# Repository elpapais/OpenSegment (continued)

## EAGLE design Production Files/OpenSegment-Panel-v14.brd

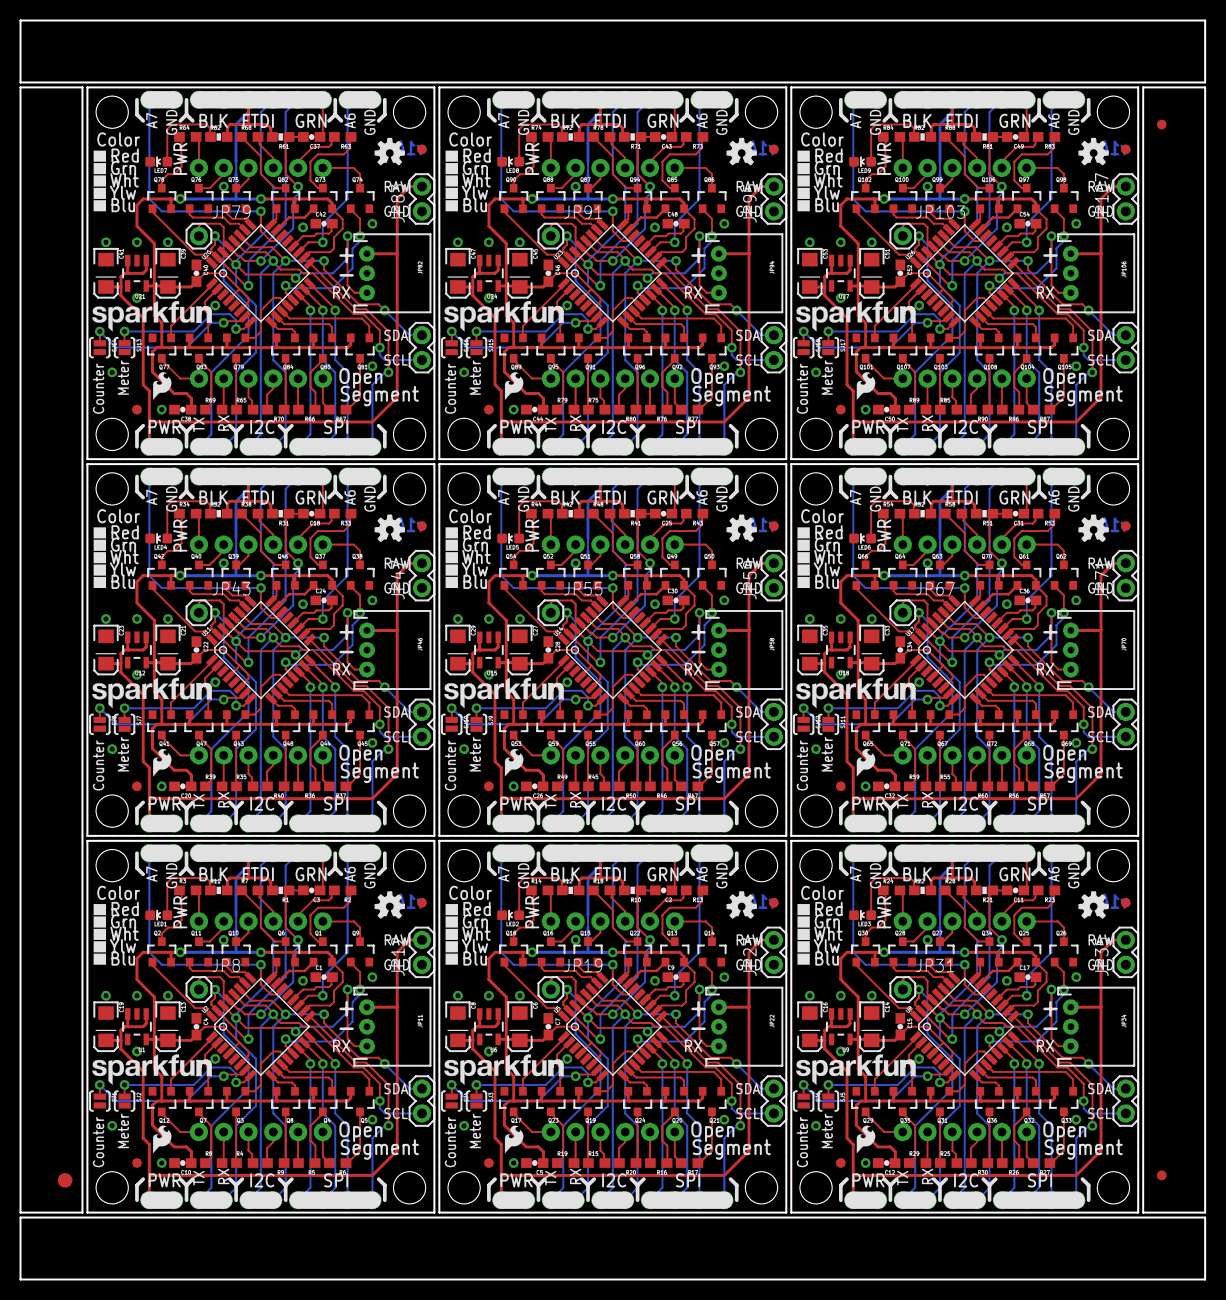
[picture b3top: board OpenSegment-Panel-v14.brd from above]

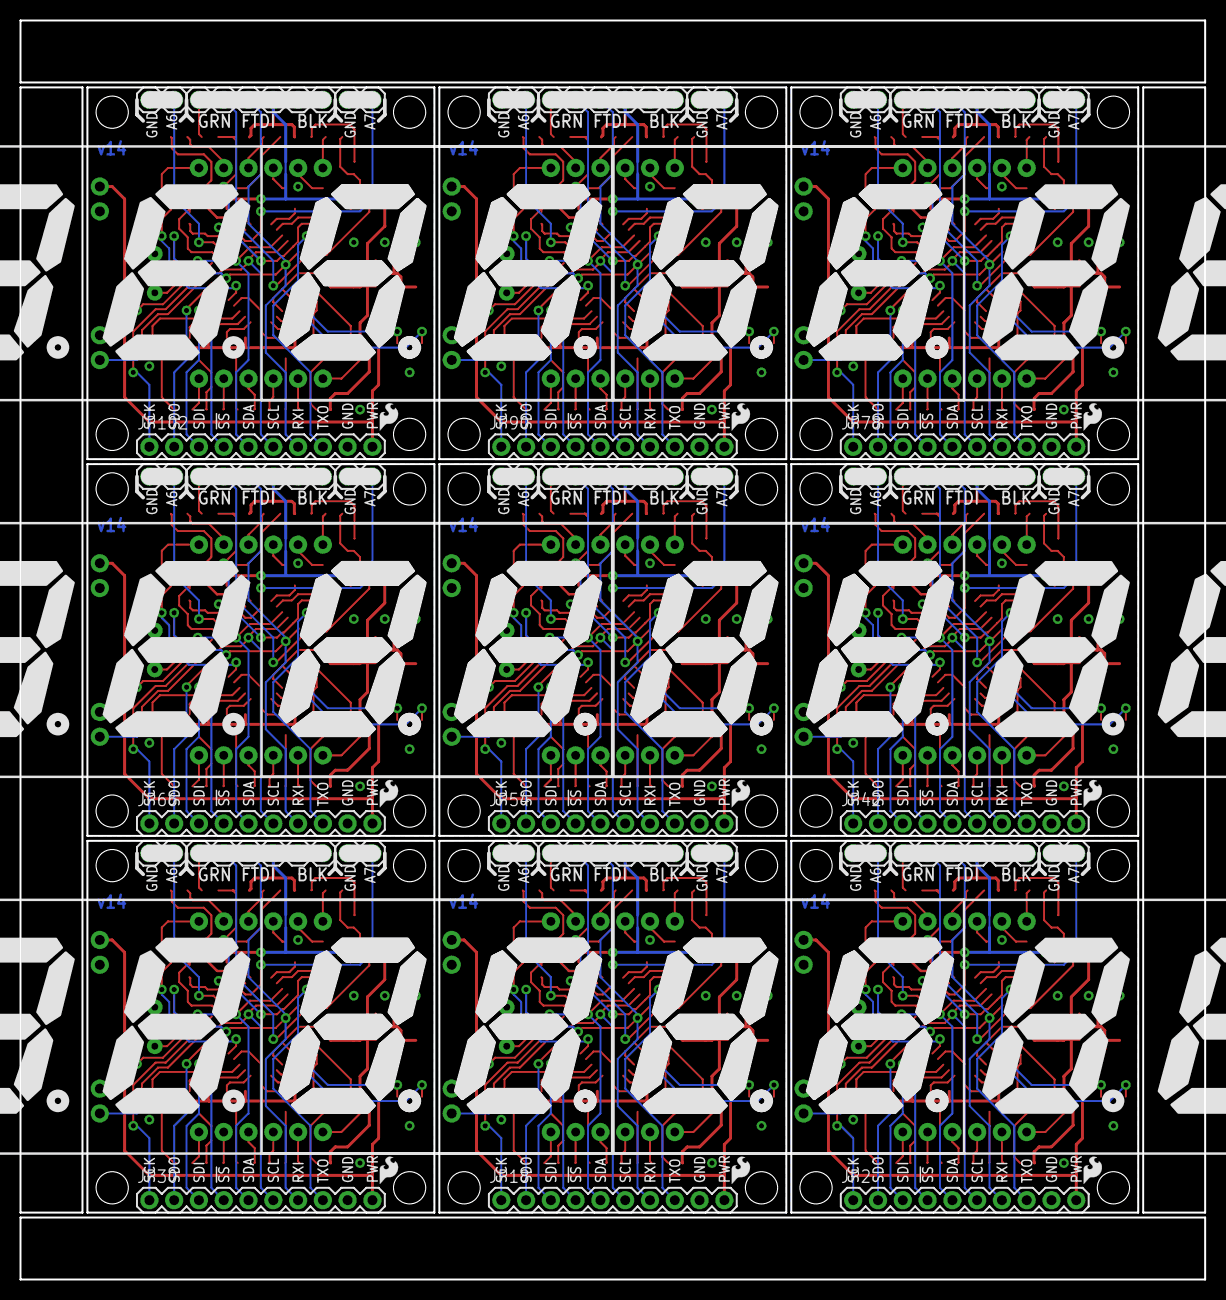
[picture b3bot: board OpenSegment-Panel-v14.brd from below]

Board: 2 copper layers, 121.4 x 129.0 mm, 471 parts (54 on the bottom side), 459 nets.

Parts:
C1, C2, C3, C4, C7, C9, C11, C15, C17, C18, C22, C24, C25, C28, C30, C31, C34, C36, C37, C40, C42, C43, C46, C48, C49, C52, C54: 0.1uF; 0603-CAP
C5, C10, C12, C20, C26, C32, C38, C44, C50: 1uF; 0603-CAP
C6, C8, C13, C14, C16, C19, C21, C23, C27, C29, C33, C35, C39, C41, C45, C47, C51, C53: 10uF; EIA3216
E$1: FIDUCIAL-1.5X3
E$4, E$5: FIDUCIAL-1X2
FID1, FID2, FID3, FID4, FID5, FID6, FID7, FID8, FID9, FID10, FID11, FID12, FID13, FID14, FID15, FID16, FID17, FID18: FIDUCIAL1X2; FIDUCIAL-1X2
JP1, JP7, JP25, JP37, JP49, JP61, JP73, JP85, JP97: FTDI_BASIC
JP2, JP18, JP30, JP42, JP54, JP66, JP78, JP90, JP102: Connections; 1X10
JP3, JP4, JP5, JP6, JP14, JP15, JP16, JP17, JP26, JP27, JP28, JP29, JP38, JP39, JP40, JP41, JP50, JP51, JP52, JP53, JP62, JP63, JP64, JP65, JP74, JP75, JP76, JP77, JP86, JP87, JP88, JP89, JP98, JP99, JP100, JP101: STAND-OFF
JP8, JP19, JP31, JP43, JP55, JP67, JP79, JP91, JP103: RESET; 1X01
JP9, JP10, JP12, JP13, JP20, JP21, JP23, JP24, JP32, JP33, JP35, JP36, JP44, JP45, JP47, JP48, JP56, JP57, JP59, JP60, JP68, JP69, JP71, JP72, JP80, JP81, JP83, JP84, JP92, JP93, JP95, JP96, JP104, JP105, JP107, JP108: 1X02
JP11, JP22, JP34, JP46, JP58, JP70, JP82, JP94, JP106: Serial; JST-3-PTH
LED1, LED2, LED3, LED4, LED5, LED6, LED7, LED8, LED9: Red; LED-0603
Q1, Q2, Q3, Q4, Q5, Q6, Q7, Q8, Q13, Q18, Q19, Q20, Q21, Q22, Q23, Q24, Q25, Q30, Q31, Q32, Q33, Q34, Q35, Q36, Q37, Q42, Q43, Q44, Q45, Q46, Q47, Q48, Q49, Q54, Q55, Q56, Q57, Q58, Q59, Q60, Q61, Q66, Q67, Q68, Q69, Q70, Q71, Q72, Q73, Q78, Q79, Q80, Q81, Q82, Q83, Q84, Q85, Q90, Q91, Q92, Q93, Q94, Q95, Q96, Q97, Q102, Q103, Q104, Q105, Q106, Q107, Q108: PNP; SOT23-3
Q9, Q10, Q11, Q12, Q14, Q15, Q16, Q17, Q26, Q27, Q28, Q29, Q38, Q39, Q40, Q41, Q50, Q51, Q52, Q53, Q62, Q63, Q64, Q65, Q74, Q75, Q76, Q77, Q86, Q87, Q88, Q89, Q98, Q99, Q100, Q101: MMBT2222; SOT23-3
R1, R10, R21, R31, R41, R51, R61, R71, R81: 10k; 0603-RES
R2, R3, R4, R5, R6, R7, R8, R9, R13, R14, R15, R16, R17, R18, R19, R20, R23, R24, R25, R26, R27, R28, R29, R30, R33, R34, R35, R36, R37, R38, R39, R40, R43, R44, R45, R46, R47, R48, R49, R50, R53, R54, R55, R56, R57, R58, R59, R60, R63, R64, R65, R66, R67, R68, R69, R70, R73, R74, R75, R76, R77, R78, R79, R80, R83, R84, R85, R86, R87, R88, R89, R90: 33/68; 0603
R11, R12, R22, R32, R42, R52, R62, R72, R82: 330; 0603-RES
SJ1, SJ2, SJ3, SJ4, SJ5, SJ6, SJ7, SJ8, SJ9, SJ10, SJ11, SJ12, SJ13, SJ14, SJ15, SJ16, SJ17, SJ18: Counter Ctl; SJ_2S-NO
U1, U6, U9, U12, U15, U18, U21, U24, U27: MIC5219; SOT23-5
U2, U5, U8, U11, U14, U17, U20, U23, U26: ATMEGA328; TQFP32-08
U3, U4, U7, U10, U13, U16, U19, U22, U25: 7-SEGMENT-4DIGIT-COUNTERPTH; 7-SEGMENT-4DIGIT-COUNTER
U$1, U$2, U$5, U$6, U$10, U$11, U$14, U$15, U$18, U$19, U$22, U$23, U$26, U$27, U$30, U$31, U$34, U$35: LOGO-SFESK; SFE-LOGO-FLAME
U$3, U$7, U$9, U$13, U$17, U$21, U$25, U$29, U$33: LOGO-SFENW2; SFE-NEW-WEB
U$4, U$8, U$12, U$16, U$20, U$24, U$28, U$32, U$36: OSHW-LOGOS; OSHW-LOGO-S

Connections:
!SS: JP2.4, U2.14
!SS1: JP18.4, U5.14
!SS2: JP30.4, U8.14
!SS3: JP42.4, U11.14
!SS4: JP54.4, U14.14
!SS5: JP66.4, U17.14
!SS6: JP78.4, U20.14
!SS7: JP90.4, U23.14
!SS8: JP102.4, U26.14
A1: JP20.2, U5.19
A2: JP21.2, U5.22
A3: JP32.2, U8.19
A4: JP33.2, U8.22
A5: JP44.2, U11.19
A6: JP9.2, U2.19
A7: JP10.2, U2.22
A8: JP45.2, U11.22
A9: JP56.2, U14.19
A10: JP57.2, U14.22
A11: JP68.2, U17.19
A12: JP69.2, U17.22
A13: JP80.2, U20.19
A14: JP81.2, U20.22
A15: JP92.2, U23.19
A16: JP93.2, U23.22
A17: JP104.2, U26.19
A18: JP105.2, U26.22
ANALOG: SJ2.1, U2.8
ANALOG1: SJ3.1, U5.8
ANALOG2: SJ5.1, U8.8
ANALOG3: SJ7.1, U11.8
ANALOG4: SJ9.1, U14.8
ANALOG5: SJ11.1, U17.8
ANALOG6: SJ13.1, U20.8
ANALOG7: SJ15.1, U23.8
ANALOG8: SJ17.1, U26.8
C-DIG1: Q9.1, U2.13
C-DIG2: Q10.1, U2.25
C-DIG3: Q11.1, U2.26
C-DIG4: Q12.1, U2.1
C-DIG5: Q14.1, U5.13
C-DIG6: Q15.1, U5.25
C-DIG7: Q16.1, U5.26
C-DIG8: Q17.1, U5.1
C-DIG9: Q26.1, U8.13
C-DIG10: Q27.1, U8.25
C-DIG11: Q28.1, U8.26
C-DIG12: Q29.1, U8.1
C-DIG13: Q38.1, U11.13
C-DIG14: Q39.1, U11.25
C-DIG15: Q40.1, U11.26
C-DIG16: Q41.1, U11.1
C-DIG17: Q50.1, U14.13
C-DIG18: Q51.1, U14.25
C-DIG19: Q52.1, U14.26
C-DIG20: Q53.1, U14.1
C-DIG21: Q62.1, U17.13
C-DIG22: Q63.1, U17.25
C-DIG23: Q64.1, U17.26
C-DIG24: Q65.1, U17.1
C-DIG25: Q74.1, U20.13
C-DIG26: Q75.1, U20.25
C-DIG27: Q76.1, U20.26
C-DIG28: Q77.1, U20.1
C-DIG29: Q86.1, U23.13
C-DIG30: Q87.1, U23.25
C-DIG31: Q88.1, U23.26
C-DIG32: Q89.1, U23.1
C-DIG33: Q98.1, U26.13
C-DIG34: Q99.1, U26.25
C-DIG35: Q100.1, U26.26
C-DIG36: Q101.1, U26.1
C-SEGA: Q1.1, U2.23
C-SEGA1: Q13.1, U5.23
C-SEGA2: Q25.1, U8.23
C-SEGA3: Q37.1, U11.23
C-SEGA4: Q49.1, U14.23
C-SEGA5: Q61.1, U17.23
C-SEGA6: Q73.1, U20.23
C-SEGA7: Q85.1, U23.23
C-SEGA8: Q97.1, U26.23
C-SEGB: Q2.1, U2.32
C-SEGB1: Q18.1, U5.32
C-SEGB2: Q30.1, U8.32
C-SEGB3: Q42.1, U11.32
C-SEGB4: Q54.1, U14.32
C-SEGB5: Q66.1, U17.32
C-SEGB6: Q78.1, U20.32
C-SEGB7: Q90.1, U23.32
C-SEGB8: Q102.1, U26.32
C-SEGC: Q3.1, U2.12
C-SEGC1: Q19.1, U5.12
C-SEGC2: Q31.1, U8.12
C-SEGC3: Q43.1, U11.12
C-SEGC4: Q55.1, U14.12
C-SEGC5: Q67.1, U17.12
C-SEGC6: Q79.1, U20.12
C-SEGC7: Q91.1, U23.12
C-SEGC8: Q103.1, U26.12
C-SEGD: Q4.1, U2.10
C-SEGD1: Q20.1, U5.10
C-SEGD2: Q32.1, U8.10
C-SEGD3: Q44.1, U11.10
C-SEGD4: Q56.1, U14.10
C-SEGD5: Q68.1, U17.10
C-SEGD6: Q80.1, U20.10
C-SEGD7: Q92.1, U23.10
C-SEGD8: Q104.1, U26.10
C-SEGDP: Q8.1, U2.9
C-SEGDP1: Q24.1, U5.9
C-SEGDP2: Q36.1, U8.9
C-SEGDP3: Q48.1, U11.9
C-SEGDP4: Q60.1, U14.9
C-SEGDP5: Q72.1, U17.9
C-SEGDP6: Q84.1, U20.9
C-SEGDP7: Q96.1, U23.9
C-SEGDP8: Q108.1, U26.9
C-SEGE: Q5.1, U2.11
C-SEGE1: Q21.1, U5.11
C-SEGE2: Q33.1, U8.11
C-SEGE3: Q45.1, U11.11
C-SEGE4: Q57.1, U14.11
C-SEGE5: Q69.1, U17.11
C-SEGE6: Q81.1, U20.11
C-SEGE7: Q93.1, U23.11
C-SEGE8: Q105.1, U26.11
C-SEGF: Q6.1, U2.24
C-SEGF1: Q22.1, U5.24
C-SEGF2: Q34.1, U8.24
C-SEGF3: Q46.1, U11.24
C-SEGF4: Q58.1, U14.24
C-SEGF5: Q70.1, U17.24
C-SEGF6: Q82.1, U20.24
C-SEGF7: Q94.1, U23.24
C-SEGF8: Q106.1, U26.24
C-SEGG: Q7.1, U2.2
C-SEGG1: Q23.1, U5.2
C-SEGG2: Q35.1, U8.2
C-SEGG3: Q47.1, U11.2
C-SEGG4: Q59.1, U14.2
C-SEGG5: Q71.1, U17.2
C-SEGG6: Q83.1, U20.2
C-SEGG7: Q95.1, U23.2
C-SEGG8: Q107.1, U26.2
COUNTER: SJ1.1, U2.7
COUNTER1: SJ4.1, U5.7
COUNTER2: SJ6.1, U8.7
COUNTER3: SJ8.1, U11.7
COUNTER4: SJ10.1, U14.7
COUNTER5: SJ12.1, U17.7
COUNTER6: SJ14.1, U20.7
COUNTER7: SJ16.1, U23.7
COUNTER8: SJ18.1, U26.7
DIG1: Q9.3, U3.12
DIG2: Q10.3, U3.9
DIG3: Q11.3, U3.8
DIG4: Q12.3, U3.6
DIG5: Q14.3, U4.12
DIG6: Q15.3, U4.9
DIG7: Q16.3, U4.8
DIG8: Q17.3, U4.6
DIG9: Q26.3, U7.12
DIG10: Q27.3, U7.9
DIG11: Q28.3, U7.8
DIG12: Q29.3, U7.6
DIG13: Q38.3, U10.12
DIG14: Q39.3, U10.9
DIG15: Q40.3, U10.8
DIG16: Q41.3, U10.6
DIG17: Q50.3, U13.12
DIG18: Q51.3, U13.9
DIG19: Q52.3, U13.8
DIG20: Q53.3, U13.6
DIG21: Q62.3, U16.12
DIG22: Q63.3, U16.9
DIG23: Q64.3, U16.8
DIG24: Q65.3, U16.6
DIG25: Q74.3, U19.12
DIG26: Q75.3, U19.9
DIG27: Q76.3, U19.8
DIG28: Q77.3, U19.6
DIG29: Q86.3, U22.12
DIG30: Q87.3, U22.9
DIG31: Q88.3, U22.8
DIG32: Q89.3, U22.6
DIG33: Q98.3, U25.12
DIG34: Q99.3, U25.9
DIG35: Q100.3, U25.8
DIG36: Q101.3, U25.6
GND: C1.1, C4.1, C10.2, C13.C, C19.C, JP1.GND, JP2.9, JP9.1, JP10.1, JP11.2, JP12.1, LED1.C, Q9.2, Q10.2, Q11.2, Q12.2, SJ1.2, SJ2.2, U1.2, U2.3, U2.5, U2.21
GND1: C5.2, C6.C, C7.1, C8.C, C9.1, JP7.GND, JP18.9, JP20.1, JP21.1, JP22.2, JP23.1, LED2.C, Q14.2, Q15.2, Q16.2, Q17.2, SJ3.2, SJ4.2, U5.3, U5.5, U5.21, U6.2
GND2: C12.2, C14.C, C15.1, C16.C, C17.1, JP25.GND, JP30.9, JP32.1, JP33.1, JP34.2, JP35.1, LED3.C, Q26.2, Q27.2, Q28.2, Q29.2, SJ5.2, SJ6.2, U8.3, U8.5, U8.21, U9.2
GND3: C20.2, C21.C, C22.1, C23.C, C24.1, JP37.GND, JP42.9, JP44.1, JP45.1, JP46.2, JP47.1, LED4.C, Q38.2, Q39.2, Q40.2, Q41.2, SJ7.2, SJ8.2, U11.3, U11.5, U11.21, U12.2
GND4: C26.2, C27.C, C28.1, C29.C, C30.1, JP49.GND, JP54.9, JP56.1, JP57.1, JP58.2, JP59.1, LED5.C, Q50.2, Q51.2, Q52.2, Q53.2, SJ9.2, SJ10.2, U14.3, U14.5, U14.21, U15.2
GND5: C32.2, C33.C, C34.1, C35.C, C36.1, JP61.GND, JP66.9, JP68.1, JP69.1, JP70.2, JP71.1, LED6.C, Q62.2, Q63.2, Q64.2, Q65.2, SJ11.2, SJ12.2, U17.3, U17.5, U17.21, U18.2
GND6: C38.2, C39.C, C40.1, C41.C, C42.1, JP73.GND, JP78.9, JP80.1, JP81.1, JP82.2, JP83.1, LED7.C, Q74.2, Q75.2, Q76.2, Q77.2, SJ13.2, SJ14.2, U20.3, U20.5, U20.21, U21.2
GND7: C44.2, C45.C, C46.1, C47.C, C48.1, JP85.GND, JP90.9, JP92.1, JP93.1, JP94.2, JP95.1, LED8.C, Q86.2, Q87.2, Q88.2, Q89.2, SJ15.2, SJ16.2, U23.3, U23.5, U23.21, U24.2
GND8: C50.2, C51.C, C52.1, C53.C, C54.1, JP97.GND, JP102.9, JP104.1, JP105.1, JP106.2, JP107.1, LED9.C, Q98.2, Q99.2, Q100.2, Q101.2, SJ17.2, SJ18.2, U26.3, U26.5, U26.21, U27.2
unnamed: Q1.3, R2.1
unnamed: C2.1, JP7.DTR
unnamed: C3.1, JP1.DTR
unnamed: Q2.3, R3.1
unnamed: Q3.3, R4.1
unnamed: Q4.3, R5.1
unnamed: Q5.3, R6.1
unnamed: Q6.3, R7.1
unnamed: Q7.3, R8.1
unnamed: Q8.3, R9.1
unnamed: C1.2, U2.20
unnamed: LED2.A, R12.1
unnamed: Q13.3, R13.1
unnamed: Q18.3, R14.1
unnamed: Q19.3, R15.1
unnamed: Q20.3, R16.1
unnamed: Q21.3, R17.1
unnamed: Q22.3, R18.1
unnamed: Q23.3, R19.1
unnamed: Q24.3, R20.1
unnamed: C9.2, U5.20
unnamed: C11.1, JP25.DTR
unnamed: LED3.A, R22.1
unnamed: Q25.3, R23.1
unnamed: Q30.3, R24.1
unnamed: Q31.3, R25.1
unnamed: Q32.3, R26.1
unnamed: Q33.3, R27.1
unnamed: Q34.3, R28.1
unnamed: Q35.3, R29.1
unnamed: Q36.3, R30.1
unnamed: C17.2, U8.20
unnamed: C18.1, JP37.DTR
unnamed: LED4.A, R32.1
unnamed: Q37.3, R33.1
unnamed: Q42.3, R34.1
unnamed: Q43.3, R35.1
unnamed: LED1.A, R11.1
unnamed: Q44.3, R36.1
unnamed: Q45.3, R37.1
unnamed: Q46.3, R38.1
unnamed: Q47.3, R39.1
unnamed: Q48.3, R40.1
unnamed: C24.2, U11.20
unnamed: C25.1, JP49.DTR
unnamed: LED5.A, R42.1
unnamed: Q49.3, R43.1
unnamed: Q54.3, R44.1
unnamed: Q55.3, R45.1
unnamed: Q56.3, R46.1
unnamed: Q57.3, R47.1
unnamed: Q58.3, R48.1
unnamed: Q59.3, R49.1
unnamed: Q60.3, R50.1
unnamed: C30.2, U14.20
unnamed: C31.1, JP61.DTR
unnamed: LED6.A, R52.1
unnamed: Q61.3, R53.1
unnamed: Q66.3, R54.1
unnamed: Q67.3, R55.1
unnamed: Q68.3, R56.1
unnamed: Q69.3, R57.1
unnamed: Q70.3, R58.1
unnamed: Q71.3, R59.1
unnamed: Q72.3, R60.1
unnamed: C36.2, U17.20
unnamed: C37.1, JP73.DTR
unnamed: LED7.A, R62.1
unnamed: Q73.3, R63.1
unnamed: Q78.3, R64.1
unnamed: Q79.3, R65.1
unnamed: Q80.3, R66.1
unnamed: Q81.3, R67.1
unnamed: Q82.3, R68.1
unnamed: Q83.3, R69.1
unnamed: Q84.3, R70.1
unnamed: C42.2, U20.20
unnamed: C43.1, JP85.DTR
unnamed: LED8.A, R72.1
unnamed: Q85.3, R73.1
unnamed: Q90.3, R74.1
unnamed: Q91.3, R75.1
unnamed: Q92.3, R76.1
unnamed: Q93.3, R77.1
unnamed: Q94.3, R78.1
unnamed: Q95.3, R79.1
unnamed: Q96.3, R80.1
unnamed: C48.2, U23.20
unnamed: C49.1, JP97.DTR
unnamed: LED9.A, R82.1
unnamed: Q97.3, R83.1
unnamed: Q102.3, R84.1
unnamed: Q103.3, R85.1
unnamed: Q104.3, R86.1
unnamed: Q105.3, R87.1
unnamed: Q106.3, R88.1
unnamed: Q107.3, R89.1
unnamed: Q108.3, R90.1
unnamed: C54.2, U26.20
RAW: C19.A, JP2.10, JP11.1, JP12.2, U1.1, U1.3
RAW1: C8.A, JP18.10, JP22.1, JP23.2, U6.1, U6.3
RAW2: C16.A, JP30.10, JP34.1, JP35.2, U9.1, U9.3
RAW3: C23.A, JP42.10, JP46.1, JP47.2, U12.1, U12.3
RAW4: C29.A, JP54.10, JP58.1, JP59.2, U15.1, U15.3
RAW5: C35.A, JP66.10, JP70.1, JP71.2, U18.1, U18.3
RAW6: C41.A, JP78.10, JP82.1, JP83.2, U21.1, U21.3
RAW7: C47.A, JP90.10, JP94.1, JP95.2, U24.1, U24.3
RAW8: C53.A, JP102.10, JP106.1, JP107.2, U27.1, U27.3
RST: C3.2, JP8.1, R1.1, U2.29
RST1: C2.2, JP19.1, R10.1, U5.29
RST2: C11.2, JP31.1, R21.1, U8.29
RST3: C18.2, JP43.1, R31.1, U11.29
RST4: C25.2, JP55.1, R41.1, U14.29
RST5: C31.2, JP67.1, R51.1, U17.29
RST6: C37.2, JP79.1, R61.1, U20.29
RST7: C43.2, JP91.1, R71.1, U23.29
RST8: C49.2, JP103.1, R81.1, U26.29
RXI: JP1.TXO, JP2.7, JP11.3, U2.30
RXI1: JP7.TXO, JP18.7, JP22.3, U5.30
RXI2: JP25.TXO, JP30.7, JP34.3, U8.30
RXI3: JP37.TXO, JP42.7, JP46.3, U11.30
RXI4: JP49.TXO, JP54.7, JP58.3, U14.30
RXI5: JP61.TXO, JP66.7, JP70.3, U17.30
RXI6: JP73.TXO, JP78.7, JP82.3, U20.30
RXI7: JP85.TXO, JP90.7, JP94.3, U23.30
RXI8: JP97.TXO, JP102.7, JP106.3, U26.30
SCK: JP2.1, U2.17
SCK1: JP18.1, U5.17
SCK2: JP30.1, U8.17
SCK3: JP42.1, U11.17
SCK4: JP54.1, U14.17
SCK5: JP66.1, U17.17
SCK6: JP78.1, U20.17
SCK7: JP90.1, U23.17
SCK8: JP102.1, U26.17
SCL: JP2.6, JP13.2, U2.28
SCL1: JP18.6, JP24.2, U5.28
SCL2: JP30.6, JP36.2, U8.28
SCL3: JP42.6, JP48.2, U11.28
SCL4: JP54.6, JP60.2, U14.28
SCL5: JP66.6, JP72.2, U17.28
SCL6: JP78.6, JP84.2, U20.28
SCL7: JP90.6, JP96.2, U23.28
SCL8: JP102.6, JP108.2, U26.28
SDA: JP2.5, JP13.1, U2.27
SDA1: JP18.5, JP24.1, U5.27
SDA2: JP30.5, JP36.1, U8.27
SDA3: JP42.5, JP48.1, U11.27
SDA4: JP54.5, JP60.1, U14.27
SDA5: JP66.5, JP72.1, U17.27
SDA6: JP78.5, JP84.1, U20.27
SDA7: JP90.5, JP96.1, U23.27
SDA8: JP102.5, JP108.1, U26.27
SDI: JP2.3, U2.15
SDI1: JP18.3, U5.15
SDI2: JP30.3, U8.15
SDI3: JP42.3, U11.15
SDI4: JP54.3, U14.15
SDI5: JP66.3, U17.15
SDI6: JP78.3, U20.15
SDI7: JP90.3, U23.15
SDI8: JP102.3, U26.15
SDO: JP2.2, U2.16
SDO1: JP18.2, U5.16
SDO2: JP30.2, U8.16
SDO3: JP42.2, U11.16
SDO4: JP54.2, U14.16
SDO5: JP66.2, U17.16
SDO6: JP78.2, U20.16
SDO7: JP90.2, U23.16
SDO8: JP102.2, U26.16
SEGA: R2.2, U3.11
SEGA1: R13.2, U4.11
SEGA2: R23.2, U7.11
SEGA3: R33.2, U10.11
SEGA4: R43.2, U13.11
SEGA5: R53.2, U16.11
SEGA6: R63.2, U19.11
SEGA7: R73.2, U22.11
SEGA8: R83.2, U25.11
SEGB: R3.2, U3.7
SEGB1: R14.2, U4.7
SEGB2: R24.2, U7.7
SEGB3: R34.2, U10.7
SEGB4: R44.2, U13.7
SEGB5: R54.2, U16.7
SEGB6: R64.2, U19.7
SEGB7: R74.2, U22.7
SEGB8: R84.2, U25.7
SEGC: R4.2, U3.4
SEGC1: R15.2, U4.4
SEGC2: R25.2, U7.4
SEGC3: R35.2, U10.4
SEGC4: R45.2, U13.4
SEGC5: R55.2, U16.4
SEGC6: R65.2, U19.4
SEGC7: R75.2, U22.4
SEGC8: R85.2, U25.4
SEGD: R5.2, U3.2
SEGD1: R16.2, U4.2
SEGD2: R26.2, U7.2
SEGD3: R36.2, U10.2
SEGD4: R46.2, U13.2
SEGD5: R56.2, U16.2
SEGD6: R66.2, U19.2
SEGD7: R76.2, U22.2
SEGD8: R86.2, U25.2
SEGDP: R9.2, U3.3
SEGDP1: R20.2, U4.3
SEGDP2: R30.2, U7.3
SEGDP3: R40.2, U10.3
SEGDP4: R50.2, U13.3
SEGDP5: R60.2, U16.3
SEGDP6: R70.2, U19.3
SEGDP7: R80.2, U22.3
SEGDP8: R90.2, U25.3
SEGE: R6.2, U3.1
SEGE1: R17.2, U4.1
SEGE2: R27.2, U7.1
SEGE3: R37.2, U10.1
SEGE4: R47.2, U13.1
SEGE5: R57.2, U16.1
SEGE6: R67.2, U19.1
SEGE7: R77.2, U22.1
SEGE8: R87.2, U25.1
SEGF: R7.2, U3.10
SEGF1: R18.2, U4.10
SEGF2: R28.2, U7.10
SEGF3: R38.2, U10.10
SEGF4: R48.2, U13.10
SEGF5: R58.2, U16.10
SEGF6: R68.2, U19.10
SEGF7: R78.2, U22.10
SEGF8: R88.2, U25.10
SEGG: R8.2, U3.5
SEGG1: R19.2, U4.5
SEGG2: R29.2, U7.5
SEGG3: R39.2, U10.5
SEGG4: R49.2, U13.5
SEGG5: R59.2, U16.5
SEGG6: R69.2, U19.5
SEGG7: R79.2, U22.5
SEGG8: R89.2, U25.5
TXO: JP1.RXI, JP2.8, U2.31
TXO1: JP7.RXI, JP18.8, U5.31
TXO2: JP25.RXI, JP30.8, U8.31
TXO3: JP37.RXI, JP42.8, U11.31
TXO4: JP49.RXI, JP54.8, U14.31
TXO5: JP61.RXI, JP66.8, U17.31
TXO6: JP73.RXI, JP78.8, U20.31
TXO7: JP85.RXI, JP90.8, U23.31
TXO8: JP97.RXI, JP102.8, U26.31
VCC: C4.2, C10.1, C13.A, JP1.VCC, Q1.2, Q2.2, Q3.2, Q4.2, Q5.2, Q6.2, Q7.2, Q8.2, R1.2, R11.2, U1.5, U2.4, U2.6, U2.18
VCC1: C5.1, C6.A, C7.2, JP7.VCC, Q13.2, Q18.2, Q19.2, Q20.2, Q21.2, Q22.2, Q23.2, Q24.2, R10.2, R12.2, U5.4, U5.6, U5.18, U6.5
VCC2: C12.1, C14.A, C15.2, JP25.VCC, Q25.2, Q30.2, Q31.2, Q32.2, Q33.2, Q34.2, Q35.2, Q36.2, R21.2, R22.2, U8.4, U8.6, U8.18, U9.5
VCC3: C20.1, C21.A, C22.2, JP37.VCC, Q37.2, Q42.2, Q43.2, Q44.2, Q45.2, Q46.2, Q47.2, Q48.2, R31.2, R32.2, U11.4, U11.6, U11.18, U12.5
VCC4: C26.1, C27.A, C28.2, JP49.VCC, Q49.2, Q54.2, Q55.2, Q56.2, Q57.2, Q58.2, Q59.2, Q60.2, R41.2, R42.2, U14.4, U14.6, U14.18, U15.5
VCC5: C32.1, C33.A, C34.2, JP61.VCC, Q61.2, Q66.2, Q67.2, Q68.2, Q69.2, Q70.2, Q71.2, Q72.2, R51.2, R52.2, U17.4, U17.6, U17.18, U18.5
VCC6: C38.1, C39.A, C40.2, JP73.VCC, Q73.2, Q78.2, Q79.2, Q80.2, Q81.2, Q82.2, Q83.2, Q84.2, R61.2, R62.2, U20.4, U20.6, U20.18, U21.5
VCC7: C44.1, C45.A, C46.2, JP85.VCC, Q85.2, Q90.2, Q91.2, Q92.2, Q93.2, Q94.2, Q95.2, Q96.2, R71.2, R72.2, U23.4, U23.6, U23.18, U24.5
VCC8: C50.1, C51.A, C52.2, JP97.VCC, Q97.2, Q102.2, Q103.2, Q104.2, Q105.2, Q106.2, Q107.2, Q108.2, R81.2, R82.2, U26.4, U26.6, U26.18, U27.5

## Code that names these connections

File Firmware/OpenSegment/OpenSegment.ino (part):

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#define SEG_ON			LOW

//Define all the hardware connections
#define SEGA			14
#define SEGB			2
#define SEGC			8
#define SEGD			6
#define SEGE			7
#define SEGF			15
#define SEGG			4
#define SEGDP			5

#define DIG1			9
#define DIG2			16
#define DIG3			17
#define DIG4			3

#define SPI_CS			10
#define SPI_MOSI		11
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  digitalWrite(DIG2, DIG_OFF);
  digitalWrite(DIG3, DIG_OFF);
  digitalWrite(DIG4, DIG_OFF);
  pinMode(DIG1, OUTPUT);
  pinMode(DIG2, OUTPUT);
  pinMode(DIG3, OUTPUT);
  pinMode(DIG4, OUTPUT);

  digitalWrite(SEGA, SEG_OFF);
  digitalWrite(SEGB, SEG_OFF);
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  digitalWrite(SEGF, SEG_OFF);
  digitalWrite(SEGG, SEG_OFF);
  digitalWrite(SEGDP, SEG_OFF);
  pinMode(SEGA, OUTPUT);
  pinMode(SEGB, OUTPUT);
  pinMode(SEGC, OUTPUT);
  pinMode(SEGD, OUTPUT);
  pinMode(SEGE, OUTPUT);
  pinMode(SEGF, OUTPUT);
  pinMode(SEGG, OUTPUT);
  pinMode(SEGDP, OUTPUT);

  checkEmergencyReset(); //Look to see if the RX pin is being pulled low

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
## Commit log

2012-09-23 Original commit
    The original commit includes v1.0 that was laid out for common anode but
    the display we received was common cathode. Version 1.1 of the PCB
    layout works with common cathode.
    The code is very preliminary. We can get data back and forth using I2C
    pretty well. Eventually I need to get this connected with the updated
    version of SevSeg.
2012-09-24 Adding serial support.
    It's not working 100% yet but the basics are there.
2012-09-24 Fixed a bug that caused the buffer to continually reset. Serial works much better now.
2012-09-24 Fixed a rare case where a user could try to set the brightness to 10 which would cause a frame reset instead of setting the brightness.
2012-09-25 Fixed the problem where zeros within a number are not printed. Now works well.
2012-09-25 Added very incomplete SPI example and checkEmergenecyReset function.
2012-09-26 Initial testing of SPI interace.
    SPI works with some small delays (1 microsecond). Trying to reduce
    overhead even more.
2012-11-05 Changing v1.2 of the PCB.
    Dropped I2C jumpers. Added analog pins. Thinking about added mode select
    jumpers.
2012-11-24 Added analog, fixed RX connector, many others.
    Changed limiting resistors to 27 Ohm for greater brightness. Renamed SPI
    pins to SDO/SDI. Added mode jumpers. Added OSHW logo. Fixed 3-pin
    connector pinout.
2012-11-28 Added I2C gang pins, silk color squares, adjusted 10uF cap spot.
2012-11-29 Added fiducial markings and created panel
    preparing for mass production
2012-12-20 Removing old firmware and code examples.
    The latest firmware and code examples are located in the Serial7Segment
    repository.
2013-01-10 Added part #s for transistors and resistor calculations.
    The bias resistors on the NPN and PNPs helped. Reducing current through
    segments further to hit 10-12mA per segment when on for 25% duty cycle.
    Also added calculations for different color displays.
2013-01-10 Updated resistor values.
2013-03-30 Added dimensions to layout and dimension image.
2013-04-18 Repo structure cleanup and README update
2013-04-19 Added firmware readme.
    Because this device has firmware, I wanted to point people to the
    location of the firmware.
2014-02-24 Commit For Desk Change
    Only doing this commit so I can work at the new QC desk
2014-02-28 Cap/res changed, updated schematic
    Changed cap/res to 0603 footprints
    Updated SCH to fr-lttr also updated to our current flag standards
    Minor trace re-routing
2014-03-11 Desk Change
2014-03-13 SCH cleanup
    Sch clean up as well as new symbols for the transistors.
2014-04-02 added regular fiducials
2014-04-02 created panel v14
